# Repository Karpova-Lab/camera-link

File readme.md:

# Camera Link
This PCB connects a [Chameleon3 USB3](https://www.flir.com/products/chameleon3-usb3/?model=CM3-U3-31S4C-CS) camera to [pyControl](https://pycontrol.readthedocs.io/en/latest/).
It takes "frame grab" and "sync pulse" signals generated by pyControl and coming out of a [D-Series Breakout Board](https://github.com/Karpova-Lab/pyControl-D-series-Breakout) 
and routes them into the GPIO pins of the camera.

Additionally, the PCB has 3 controllable high power IR LEDs that provide light for the camera to see in the dark.

## PCB 
<a href="https://oshpark.com/shared_projects/eBqWROZ7"></img></a>

| Qty | Reference                | Description       | Value/MPN                                                                                                                                    | 
|-----|--------------------------|-------------------|----------------------------------------------------------------------------------------------------------------------------------------------|
| 3   | D1, D2, D3               | 850 nm LED        | [LST1-01F09-IR01-00](https://www.digikey.com/en/products/detail/new-energy/LST1-01F09-IR01-00/9445943?s=N4IgTCBcDaIIwDYDsYC0c4FYAMIC6AvkA)   | 
| 2   | H1, H2                   | Threaded standoff | [24882](https://www.digikey.com/en/products/detail/keystone-electronics/24882/9921822?s=N4IgTCBcDaIMwDYC0YAsAOdYkEYkDkAREAXQF8g)             | 
| 1   | J1                       | 9-pin socket      | [BM09B-NSHSS-TBT](https://www.digikey.com/en/products/detail/jst-sales-america-inc/BM09B-NSHSS-TBT-LF-SN/3313615)                            | 
| 1   | J2                       | RJ45 jack         | [E5J88-00LJG2-L](https://www.digikey.com/en/products/detail/pulse-electronics/E5J88-00LJG2-L/1785312?s=N4IgTCBcDaIKxwMwFoxgGwBZkDkAiIAugL5A) | 
| 1   | R1                       | 5 watt resistor   | [5Ω](https://www.digikey.com/en/products/detail/ohmite/WNE5R0FET/3114558?s=N4IgTCBcDaIOoDkCiBWATgBgGYFMAuAxniALoC%2BQA)                      | 

[View interactive BOM](https://karpova-lab.github.io/camera-link/ibom)

## Camera Hardware
- [CM3-U3](docs/CM3-U3-Technical-Reference.pdf) camera
- [A4Z2812CS-MPIR](docs/A4Z2812CS-MPIR_12-14.pdf) lens

## GPIO cable
- [9 position NSH series plug](https://www.digikey.com/en/products/detail/jst-sales-america-inc/NSHR-09V-S/3313624)
- [8" pre-crimped wires](https://www.digikey.com/en/products/detail/jst-sales-america-inc/ASSHLSSHL28K203/9924242?s=N4IgjCBcoOw1oDGUBmBDANgZwKYBoQB7KAbRACYAOcgBgFYBmEAXQIAcAXKEAZQ4CcAlgDsA5iAC+BGJQQhkkdNnxFS4AGwM6MdS3ZdIvASPFSQDMPGjzUmXAWKQyAFhrOds1iE7c+QsZIEALQQ1gpK9qpOIM50dCxmQc5y4XYqjmRg6mD0CRISQA)

| GPIO pin | GPIO Color | GPIO Function | RJ45 Pin | pyControl Function | Purpose                                                  |
|----------|------------|---------------|----------|--------------------|----------------------------------------------------------|
| 4        | Green      | GPIO3/Line3   | 1        | DIO_A              | pyControl sends square wave to camera to grab each frame |
| 9        | Yellow     | OPTO_IN/Line0 | 4        | DIO_B              | pyControl sends random sync pulse                        |
| 6        | Black      | GND           | 2        | Ground             | Ground                                                   |
| 7        | Brown      | OPTO_GND      | 2        | Ground             | Ground                                                   |

## Software
- [Bias](https://github.com/iorodeo/bias)
- [pyControl synchronization](https://pycontrol.readthedocs.io/en/latest/user-guide/synchronisation/)

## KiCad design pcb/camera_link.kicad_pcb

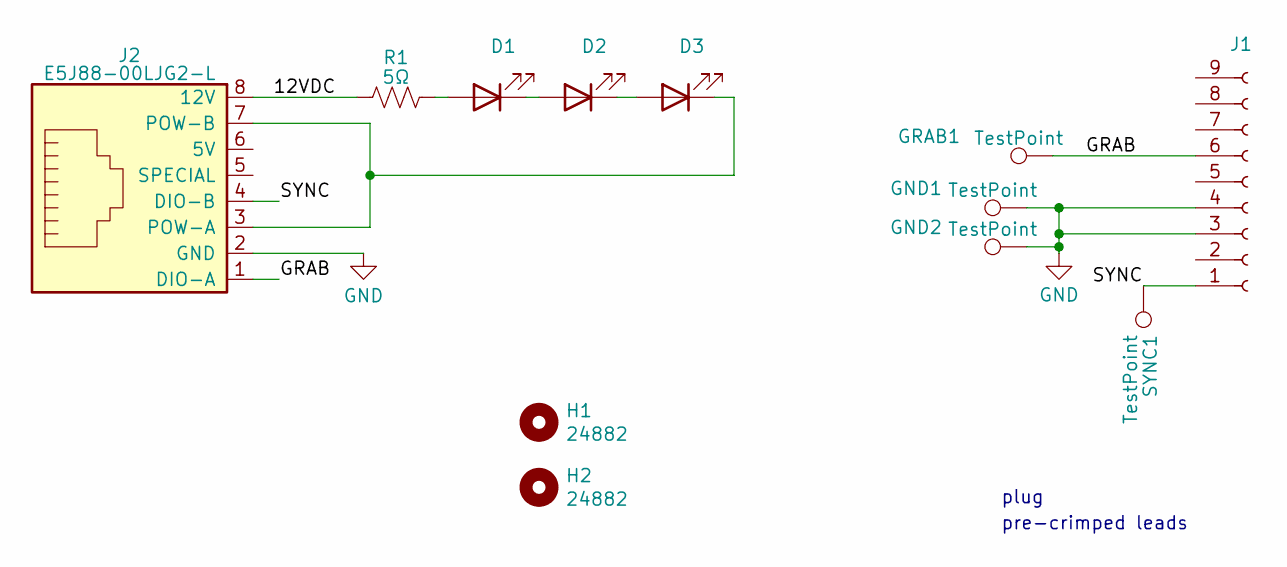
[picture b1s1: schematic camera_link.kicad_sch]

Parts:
D1, D2, D3: LST1-01F09-IR01-00; LED_starboard
GND1, GND2: TestPoint; Pin_D1.0mm_L10.0mm
GRAB1: TestPoint; Pin_D1.0mm_L10.0mm
H1, H2: 24882; standoff_nut
J1: BM09B-NSHSS-TBT; JST_NSH_1x09_VERTICAL
J2: E5J88-00LJG2-L; RJ45_THP_tab_on_top
R1: 5Ω; R_Axial_DIN0614_L14.3mm_D5.7mm_P7.62mm_Vertical
SYNC1: TestPoint; Pin_D1.0mm_L10.0mm

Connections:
/12VDC: J2.8 (12V), R1.1
/GRAB: GRAB1.1, J1.6, J2.1 (DIO-A)
/SYNC: J1.1, J2.4 (DIO-B), SYNC1.1
GND: GND1.1, GND2.1, J1.3, J1.4, J2.2 (GND)
unnamed: D1.2 (A), R1.2
unnamed: D1.1 (K), D2.2 (A)
unnamed: D2.1 (K), D3.2 (A)
unnamed: D3.1 (K), J2.3 (POW-A), J2.7 (POW-B)

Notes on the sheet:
pre-crimped leads
plug

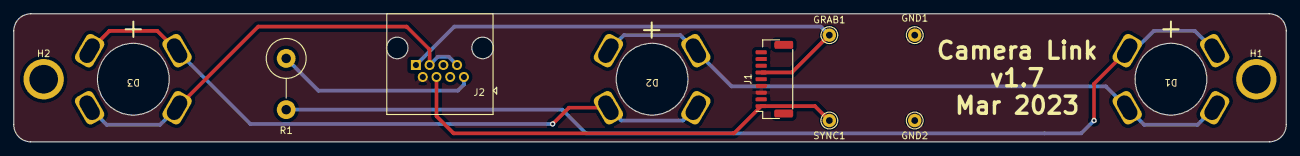
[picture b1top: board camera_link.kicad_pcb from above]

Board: 2 copper layers, 189.2 x 19.0 mm, 12 parts (0 on the bottom side), 8 nets.

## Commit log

2021-01-11 PCB v1.1
2021-01-12 pcbv1.2
2021-03-02 updated .gitignore
2021-03-02 Added gerbers and BOM
2021-03-02 Added README
2021-03-02 update readme
    added PCB link
2021-03-02 added license
2022-12-02 pcb v1.3
2023-01-04 pcb v1.5
2023-01-12 PCB v1.6
2023-05-24 pcb v1.7
2024-09-24 readme update
    - replaced broken lens link with link to datasheet
